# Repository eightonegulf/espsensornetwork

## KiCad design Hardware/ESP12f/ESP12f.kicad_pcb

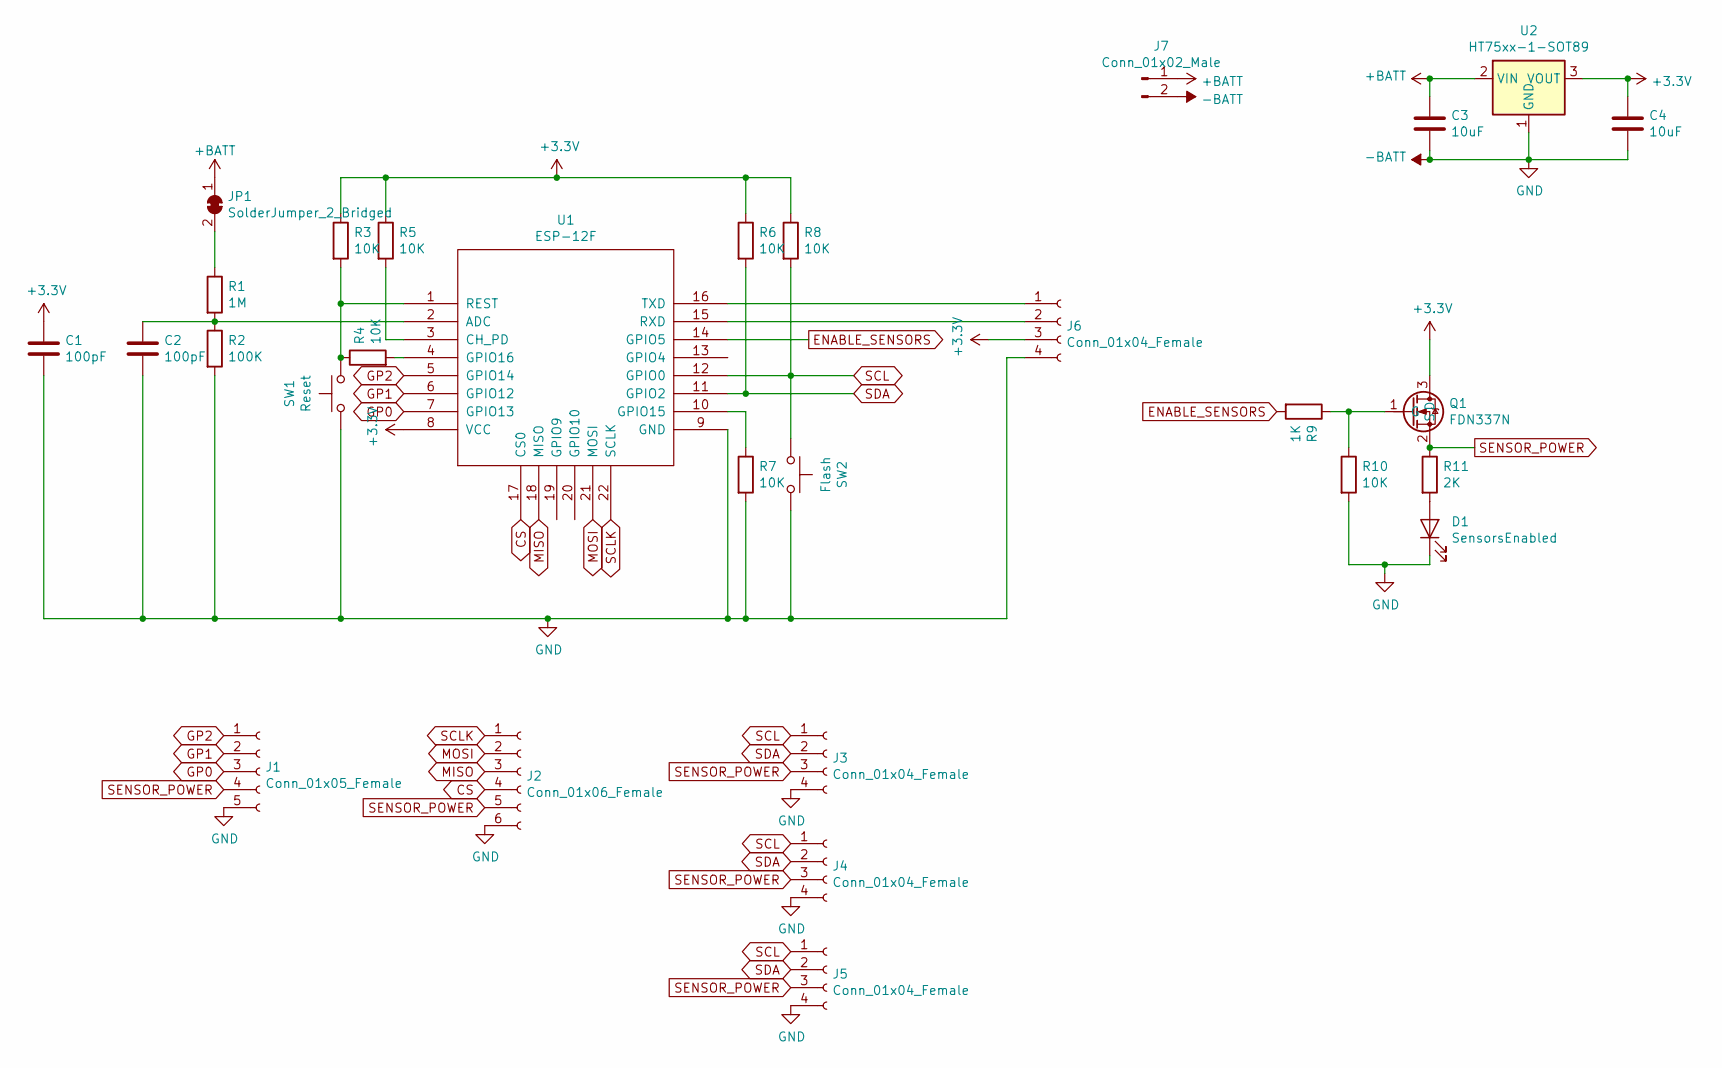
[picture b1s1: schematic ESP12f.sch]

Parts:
C1, C2: 100pF; C_0805_2012Metric_Pad1.15x1.40mm_HandSolder
C3, C4: 10uF; C_0805_2012Metric_Pad1.15x1.40mm_HandSolder
D1: SensorsEnabled; LED_0805_2012Metric_Pad1.15x1.40mm_HandSolder
J1: Conn_01x05_Female; JST_SH_BM05B-SRSS-TB_1x05-1MP_P1.00mm_Vertical
J2: Conn_01x06_Female; JST_SH_BM06B-SRSS-TB_1x06-1MP_P1.00mm_Vertical
J3, J4, J5, J6: Conn_01x04_Female; JST_SH_BM04B-SRSS-TB_1x04-1MP_P1.00mm_Vertical
J7: Conn_01x02_Male; JST_EH_S2B-EH_1x02_P2.50mm_Horizontal
JP1: SolderJumper_2_Bridged; SolderJumper-2_P1.3mm_Bridged_RoundedPad1.0x1.5mm
Q1: FDN337N; SuperSOT-3
R1: 1M; R_0805_2012Metric_Pad1.15x1.40mm_HandSolder
R2: 100K; R_0805_2012Metric_Pad1.15x1.40mm_HandSolder
R3, R4, R5, R6, R7, R8, R10: 10K; R_0805_2012Metric_Pad1.15x1.40mm_HandSolder
R9: 1K; R_0805_2012Metric_Pad1.15x1.40mm_HandSolder
R11: 2K; R_0805_2012Metric_Pad1.15x1.40mm_HandSolder
SW1: Reset; SW_Push_1P1T_NO_6x6mm_H9.5mm
SW2: Flash; SW_Push_1P1T_NO_6x6mm_H9.5mm
U1: ESP-12F; ESP-12E_SMD
U2: HT75xx-1-SOT89; SOT-89-3

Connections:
+3V3: C1.1, C4.1, J6.3, Q1.3 (D), R3.1, R5.1, R6.1, R8.1, U1.8 (VCC), U2.3 (VOUT)
+BATT: C3.1, J7.1, JP1.1 (A), U2.2 (VIN)
-BATT: C1.2, C2.2, C3.2, C4.2, D1.1 (K), J1.5, J2.6, J3.4, J4.4, J5.4, J6.4, J7.2, R2.2, R7.2, R10.2, SW1.1, SW2.2, U1.9 (GND), U2.1 (GND)
CS: J2.4, U1.17 (CS0)
ENABLE_SENSORS: R9.2, U1.14 (GPIO5)
GP0: J1.3, U1.7 (GPIO13)
GP1: J1.2, U1.6 (GPIO12)
GP2: J1.1, U1.5 (GPIO14)
MISO: J2.3, U1.18 (MISO)
MOSI: J2.2, U1.21 (MOSI)
unnamed: C2.1, R1.2, R2.1, U1.2 (ADC)
unnamed: D1.2 (A), R11.2
unnamed: J6.1, U1.16 (TXD)
unnamed: J6.2, U1.15 (RXD)
unnamed: JP1.2 (B), R1.1
unnamed: Q1.1 (G), R9.1, R10.1
unnamed: R3.2, R4.1, SW1.2, U1.1 (REST)
unnamed: R4.2, U1.4 (GPIO16)
unnamed: R5.2, U1.3 (CH_PD)
unnamed: R7.1, U1.10 (GPIO15)
SCL: J3.1, J4.1, J5.1, R8.2, SW2.1, U1.12 (GPIO0)
SCLK: J2.1, U1.22 (SCLK)
SDA: J3.2, J4.2, J5.2, R6.2, U1.11 (GPIO2)
SENSOR_POWER: J1.4, J2.5, J3.3, J4.3, J5.3, Q1.2 (S), R11.1

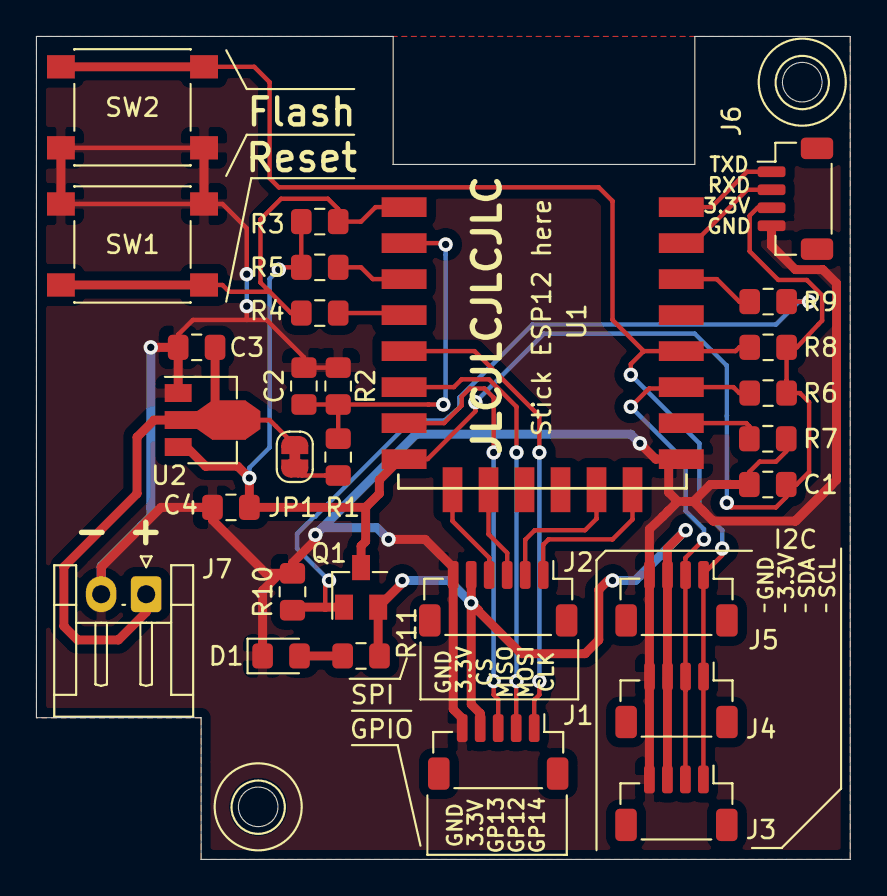
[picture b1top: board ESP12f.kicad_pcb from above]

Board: 2 copper layers, 45.2 x 45.7 mm, 29 parts (0 on the bottom side), 24 nets.

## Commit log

2020-05-09 ESP12F board
